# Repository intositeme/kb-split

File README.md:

# kb-split

Big thanks to guys on #QMK discord #hardward channel.

Very first PCB ever designed and produced. 6 cols x 4 rows + 2 extra switch & rotary Encoder
Split olkb keyboard runninf QMK Firmware

Initially designed to use Fischer EGG 0B(board side) with FGG 0B cables, though very expensive ( connectors alone are $40usd+). Added TRS footprint.

Board is reversible, though MCU sits only on 1 side.

- ATmega32u4-AU
- all leds Sk6812
- RGB Underglow & per key RGB
- 1x E11 rotary encoder

* Space bar fits up to 2u but no stabilizers

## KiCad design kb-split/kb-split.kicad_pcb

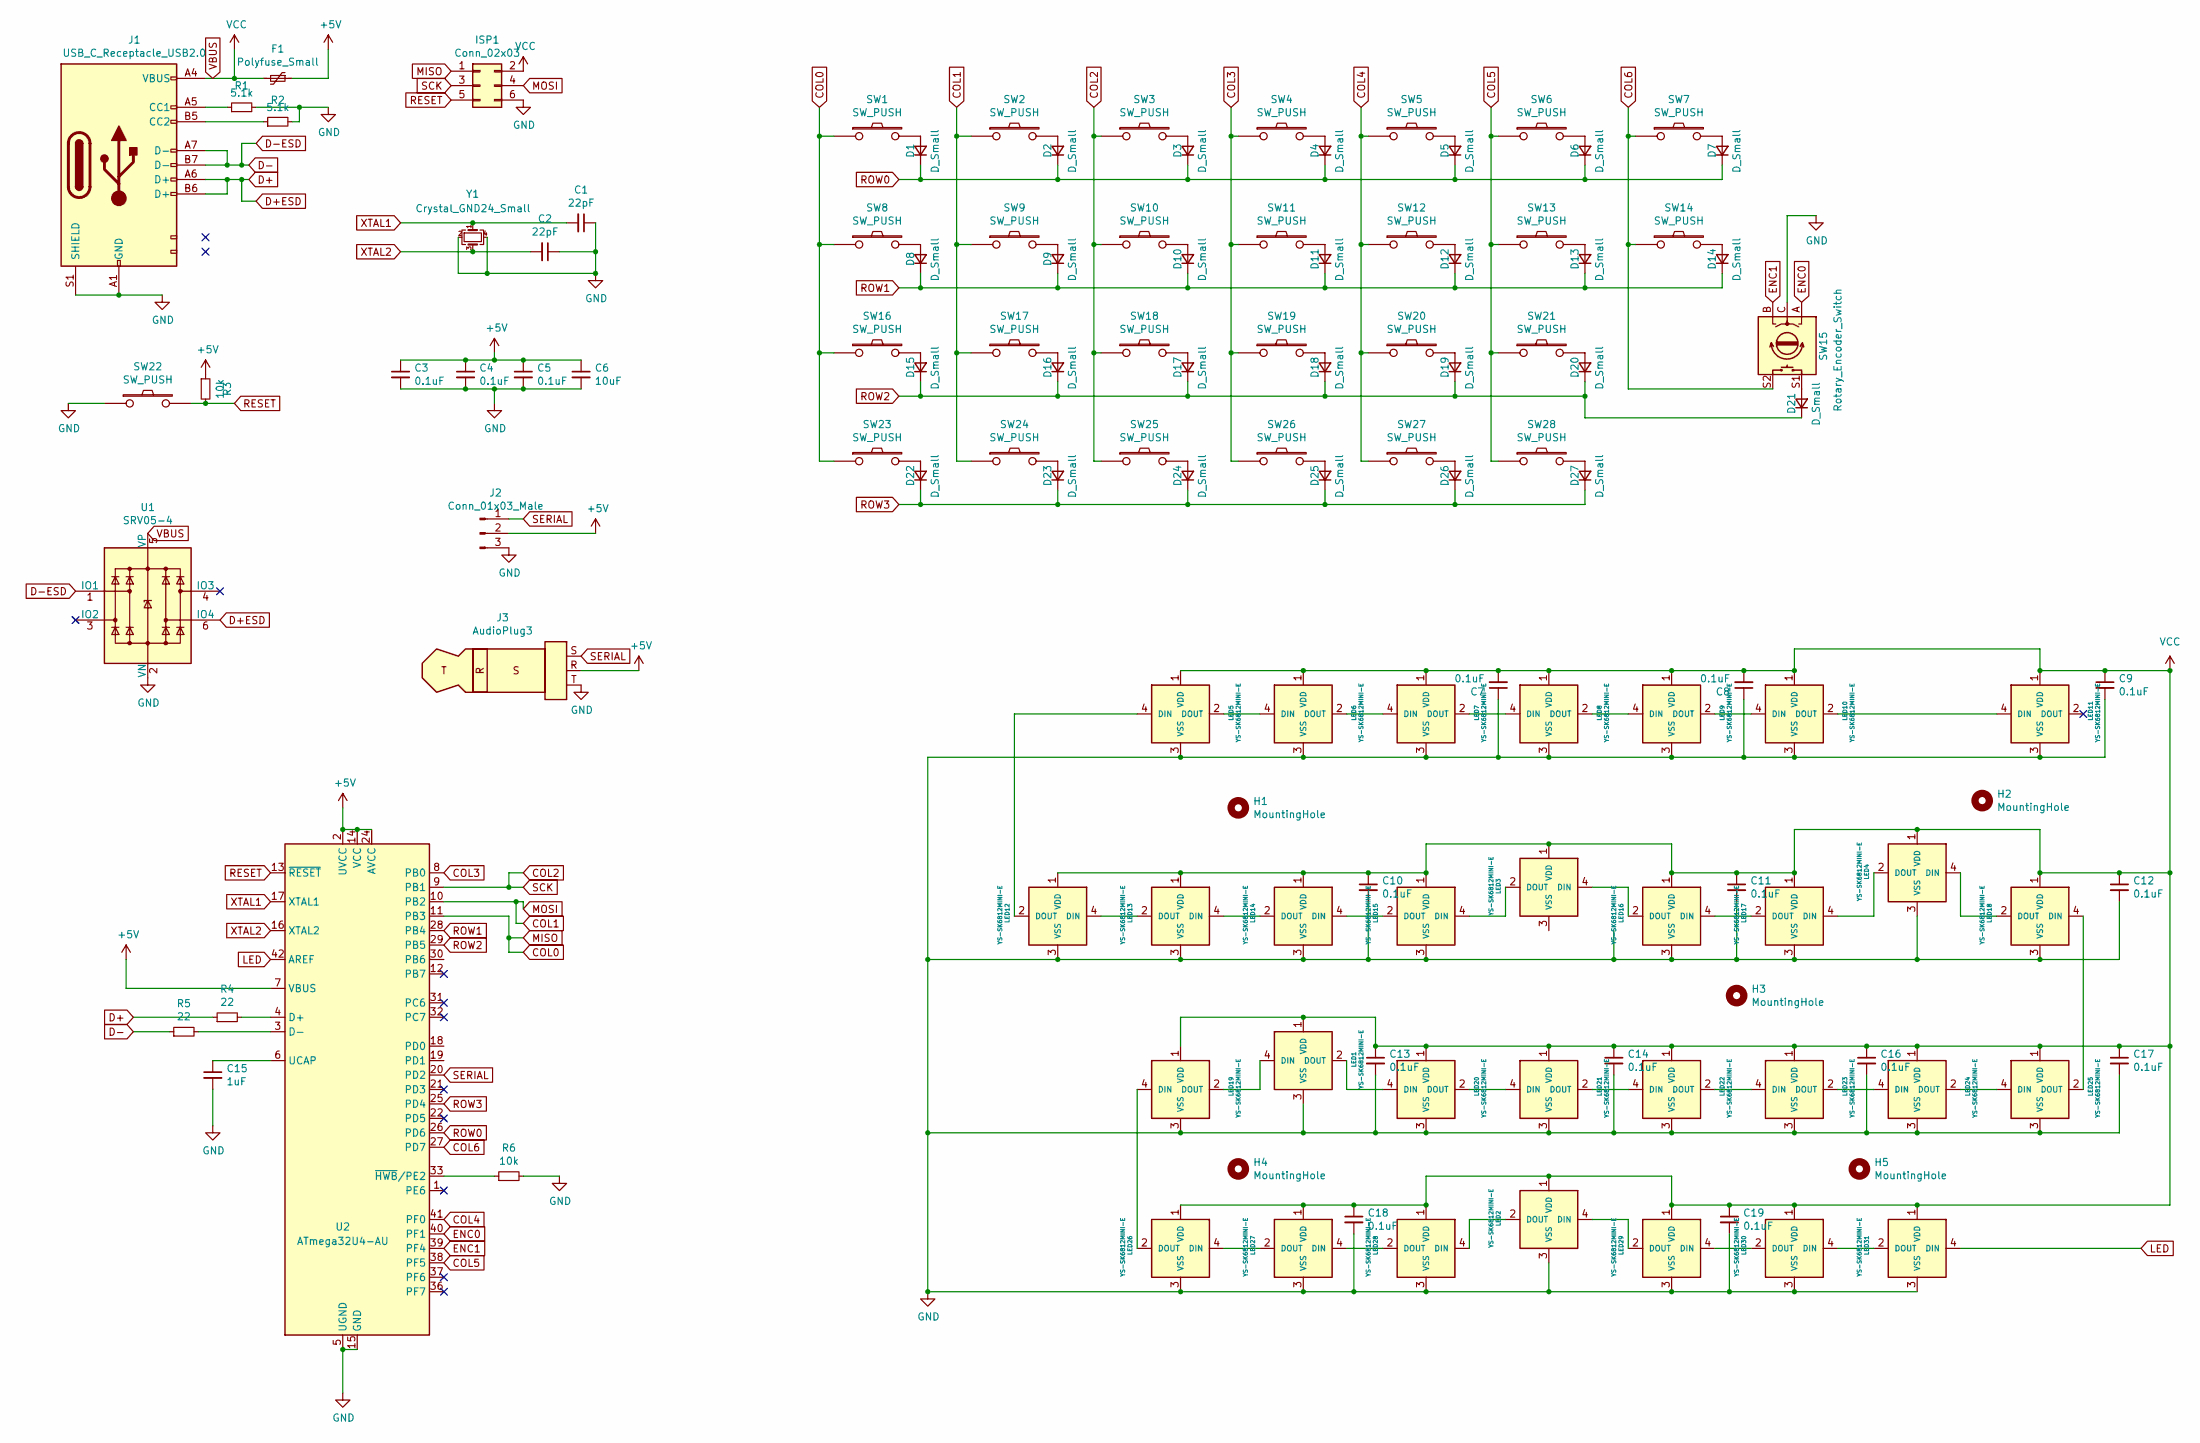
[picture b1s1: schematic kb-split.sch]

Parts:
C1, C2: 22pF; C-0805_2012Metric
C3, C4, C5, C7, C8, C9, C10, C11, C12, C13, C14, C16, C17, C18, C19: 0.1uF; C-0805_2012Metric
C6: 10uF; C-0805_2012Metric
C15: 1uF; C-0805_2012Metric
D1, D2, D3, D4, D5, D6, D7, D8, D9, D10, D11, D12, D13, D14, D15, D16, D17, D18, D19, D20, D21, D22, D23, D24, D25, D26, D27: D_Small; D_SOD-123
F1: Polyfuse_Small; Fuse_1206_3216Metric
H1, H2, H3, H4, H5: MountingHole; M2_HOLE_v3
ISP1: Conn_02x03; PinSocket_2x03_P2.54mm_Vertical
J1: USB_C_Receptacle_USB2.0; HRO-TYPE-C-31-M-12-HandSoldering-NoSBU
J2: Conn_01x03_Male; PinSocket_1x03_P2.54mm_Horizontal
J3: AudioPlug3; PJ-3136-B
LED1, LED2, LED3, LED4, LED25: YS-SK6812MINI-E; SK6812Mini-E
LED5, LED6, LED7, LED8, LED9, LED10, LED11, LED12, LED13, LED14, LED15, LED16, LED17, LED18, LED19, LED20, LED21, LED22, LED23, LED24, LED26, LED27, LED28, LED29, LED30, LED31: YS-SK6812MINI-E; MX-1U-SK6812Mini-E
R1, R2: 5.1k; R-0805_2012Metric
R3, R6: 10k; R-0805_2012Metric
R4, R5: 22; R-0805_2012Metric
SW1, SW2, SW3, SW4, SW5, SW6, SW7, SW8, SW9, SW10, SW11, SW12, SW13, SW14, SW16, SW17, SW18, SW19, SW20, SW21, SW23, SW24, SW25, SW26, SW27, SW28: SW_PUSH; MX-1U-Hotswap
SW15: Rotary_Encoder_Switch; MX-1U-EC11_Switch
SW22: SW_PUSH; SMD_Push
U1: SRV05-4; SOT-23-6
U2: ATmega32U4-AU; TQFP-44_10x10mm_P0.8mm
Y1: Crystal_GND24_Small; Reversible-Crystal_SMD_3225-4pin_3.2x2.5mm

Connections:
+5V: C3.1, C4.1, C5.1, C6.1, F1.1, J2.2, J3.R, R3.1, U2.2 (UVCC), U2.7 (VBUS), U2.14 (VCC), U2.24 (AVCC), U2.34 (VCC), U2.44 (AVCC)
COL0: ISP1.1, SW1.1, SW8.1, SW16.1, SW23.1, U2.11 (PB3)
COL1: ISP1.4, SW2.1, SW9.1, SW17.1, SW24.1, U2.10 (PB2)
COL2: ISP1.3, SW3.1, SW10.1, SW18.1, SW25.1, U2.9 (PB1)
COL3: SW4.1, SW11.1, SW19.1, SW26.1, U2.8 (PB0)
COL4: SW5.1, SW12.1, SW20.1, SW27.1, U2.41 (PF0)
COL5: SW6.1, SW13.1, SW21.1, SW28.1, U2.38 (PF5)
COL6: SW7.1, SW14.1, SW15.S2, U2.27 (PD7)
D+: J1.A6 (D+), J1.B6 (D+), R4.1, U1.6 (IO4)
D-: J1.A7 (D-), J1.B7 (D-), R5.1, U1.1 (IO1)
ENC0: SW15.A, U2.40 (PF1)
ENC1: SW15.B, U2.39 (PF4)
GND: C1.1, C2.1, C3.2, C4.2, C5.2, C6.2, C7.1, C8.1, C9.2, C10.2, C11.2, C12.2, C13.2, C14.2, C15.2, C16.2, C17.2, C18.2, C19.2, ISP1.6, J1.A1 (GND), J1.B1 (GND), J1.S1 (SHIELD), J2.3, J3.T, LED1.3 (VSS), LED2.3 (VSS), LED4.3 (VSS), LED5.3 (VSS), LED6.3 (VSS), LED7.3 (VSS), LED8.3 (VSS), LED9.3 (VSS), LED10.3 (VSS), LED11.3 (VSS), LED12.3 (VSS), LED13.3 (VSS), LED14.3 (VSS), LED15.3 (VSS), LED16.3 (VSS), LED17.3 (VSS), LED18.3 (VSS), LED19.3 (VSS), LED20.3 (VSS), LED21.3 (VSS), LED22.3 (VSS), LED23.3 (VSS), LED24.3 (VSS), LED25.3 (VSS), LED26.3 (VSS), LED27.3 (VSS), LED28.3 (VSS), LED29.3 (VSS), LED30.3 (VSS), LED31.3 (VSS), R1.2, R2.2, R6.2, SW15.C, SW22.1, U1.2 (VN), U2.5 (UGND), U2.15 (GND), U2.23 (GND), U2.35 (GND), U2.43 (GND), Y1.2, Y1.4
LED: LED31.4 (DIN), U2.42 (AREF)
unnamed: C15.1, U2.6 (UCAP)
unnamed: D1.2 (A), SW1.2
unnamed: D2.2 (A), SW2.2
unnamed: D3.2 (A), SW3.2
unnamed: D4.2 (A), SW4.2
unnamed: D5.2 (A), SW5.2
unnamed: D6.2 (A), SW6.2
unnamed: D7.2 (A), SW7.2
unnamed: D8.2 (A), SW8.2
unnamed: D9.2 (A), SW9.2
unnamed: D10.2 (A), SW10.2
unnamed: D11.2 (A), SW11.2
unnamed: D12.2 (A), SW12.2
unnamed: D13.2 (A), SW13.2
unnamed: D14.2 (A), SW14.2
unnamed: D15.2 (A), SW16.2
unnamed: D16.2 (A), SW17.2
unnamed: D17.2 (A), SW18.2
unnamed: D18.2 (A), SW19.2
unnamed: D19.2 (A), SW20.2
unnamed: D20.2 (A), SW21.2
unnamed: D21.2 (A), SW15.S1
unnamed: D22.2 (A), SW23.2
unnamed: D23.2 (A), SW24.2
unnamed: D24.2 (A), SW25.2
unnamed: D25.2 (A), SW26.2
unnamed: D26.2 (A), SW27.2
unnamed: D27.2 (A), SW28.2
unnamed: J1.A5 (CC1), R1.1
unnamed: J1.B5 (CC2), R2.1
unnamed: LED1.2 (DOUT), LED20.4 (DIN)
unnamed: LED1.4 (DIN), LED19.2 (DOUT)
unnamed: LED2.2 (DOUT), LED28.4 (DIN)
unnamed: LED2.4 (DIN), LED29.2 (DOUT)
unnamed: LED5.2 (DOUT), LED6.4 (DIN)
unnamed: LED6.2 (DOUT), LED7.4 (DIN)
unnamed: LED7.2 (DOUT), LED8.4 (DIN)
unnamed: LED8.2 (DOUT), LED9.4 (DIN)
unnamed: LED10.2 (DOUT), LED11.4 (DIN)
unnamed: LED9.2 (DOUT), LED10.4 (DIN)
unnamed: LED5.4 (DIN), LED12.2 (DOUT)
unnamed: LED12.4 (DIN), LED13.2 (DOUT)
unnamed: LED13.4 (DIN), LED14.2 (DOUT)
unnamed: LED14.4 (DIN), LED15.2 (DOUT)
unnamed: LED3.2 (DOUT), LED15.4 (DIN)
unnamed: LED3.4 (DIN), LED16.2 (DOUT)
unnamed: LED16.4 (DIN), LED17.2 (DOUT)
unnamed: LED4.2 (DOUT), LED17.4 (DIN)
unnamed: LED4.4 (DIN), LED18.2 (DOUT)
unnamed: LED18.4 (DIN), LED25.2 (DOUT)
unnamed: LED19.4 (DIN), LED26.2 (DOUT)
unnamed: LED20.2 (DOUT), LED21.4 (DIN)
unnamed: LED21.2 (DOUT), LED22.4 (DIN)
unnamed: LED22.2 (DOUT), LED23.4 (DIN)
unnamed: LED23.2 (DOUT), LED24.4 (DIN)
unnamed: LED24.2 (DOUT), LED25.4 (DIN)
unnamed: LED26.4 (DIN), LED27.2 (DOUT)
unnamed: LED27.4 (DIN), LED28.2 (DOUT)
unnamed: LED29.4 (DIN), LED30.2 (DOUT)
unnamed: LED30.4 (DIN), LED31.2 (DOUT)
unnamed: R4.2, U2.4 (D+)
unnamed: R5.2, U2.3 (D-)
unnamed: R6.1, U2.33 (~HWB~/PE2)
RESET: ISP1.5, R3.2, SW22.2, U2.13 (~RESET)
ROW0: D1.1 (K), D2.1 (K), D3.1 (K), D4.1 (K), D5.1 (K), D6.1 (K), D7.1 (K), U2.26 (PD6)
ROW1: D8.1 (K), D9.1 (K), D10.1 (K), D11.1 (K), D12.1 (K), D13.1 (K), D14.1 (K), U2.28 (PB4)
ROW2: D15.1 (K), D16.1 (K), D17.1 (K), D18.1 (K), D19.1 (K), D20.1 (K), D21.1 (K), U2.29 (PB5)
ROW3: D22.1 (K), D23.1 (K), D24.1 (K), D25.1 (K), D26.1 (K), D27.1 (K), U2.25 (PD4)
SERIAL: J2.1, J3.S, U2.20 (PD2)
VBUS: C7.2, C8.2, C9.1, C10.1, C11.1, C12.1, C13.1, C14.1, C16.1, C17.1, C18.1, C19.1, F1.2, ISP1.2, J1.A4 (VBUS), J1.B4 (VBUS), LED1.1 (VDD), LED2.1 (VDD), LED3.1 (VDD), LED4.1 (VDD), LED5.1 (VDD), LED6.1 (VDD), LED7.1 (VDD), LED8.1 (VDD), LED9.1 (VDD), LED10.1 (VDD), LED11.1 (VDD), LED12.1 (VDD), LED13.1 (VDD), LED14.1 (VDD), LED15.1 (VDD), LED16.1 (VDD), LED17.1 (VDD), LED18.1 (VDD), LED19.1 (VDD), LED20.1 (VDD), LED21.1 (VDD), LED22.1 (VDD), LED23.1 (VDD), LED24.1 (VDD), LED25.1 (VDD), LED26.1 (VDD), LED27.1 (VDD), LED28.1 (VDD), LED29.1 (VDD), LED30.1 (VDD), LED31.1 (VDD), U1.5 (VP)
XTAL1: C1.2, U2.17 (XTAL1), Y1.1
XTAL2: C2.2, U2.16 (XTAL2), Y1.3

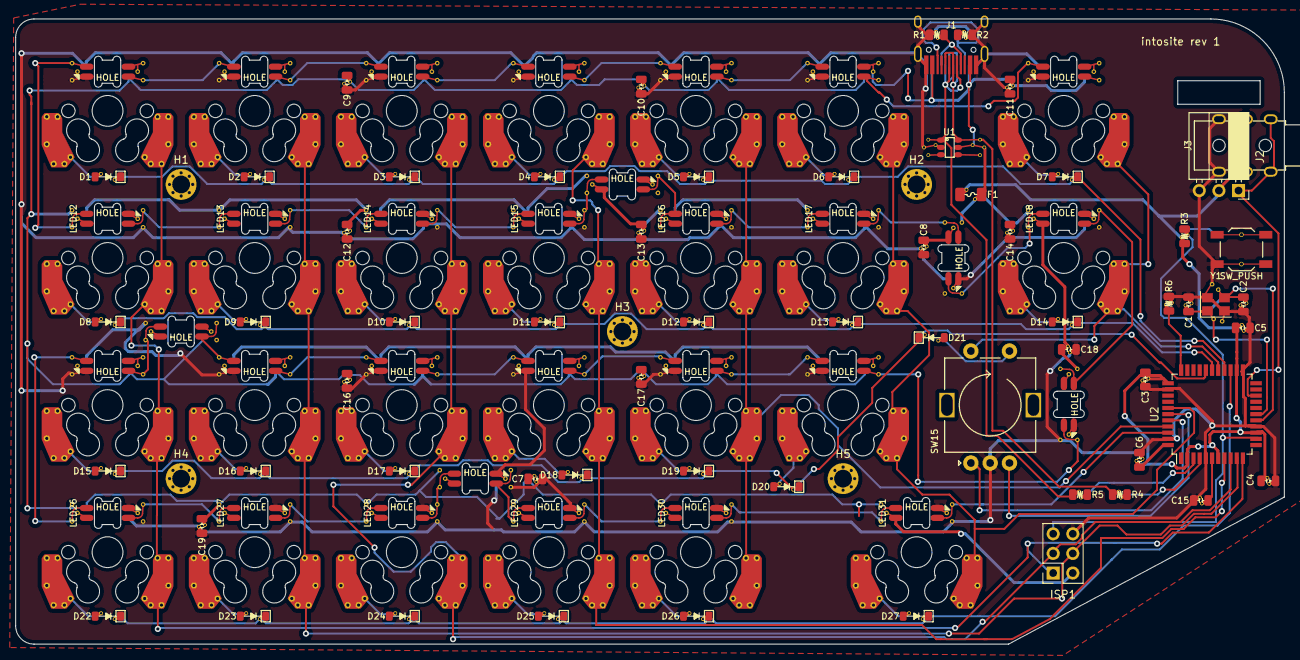
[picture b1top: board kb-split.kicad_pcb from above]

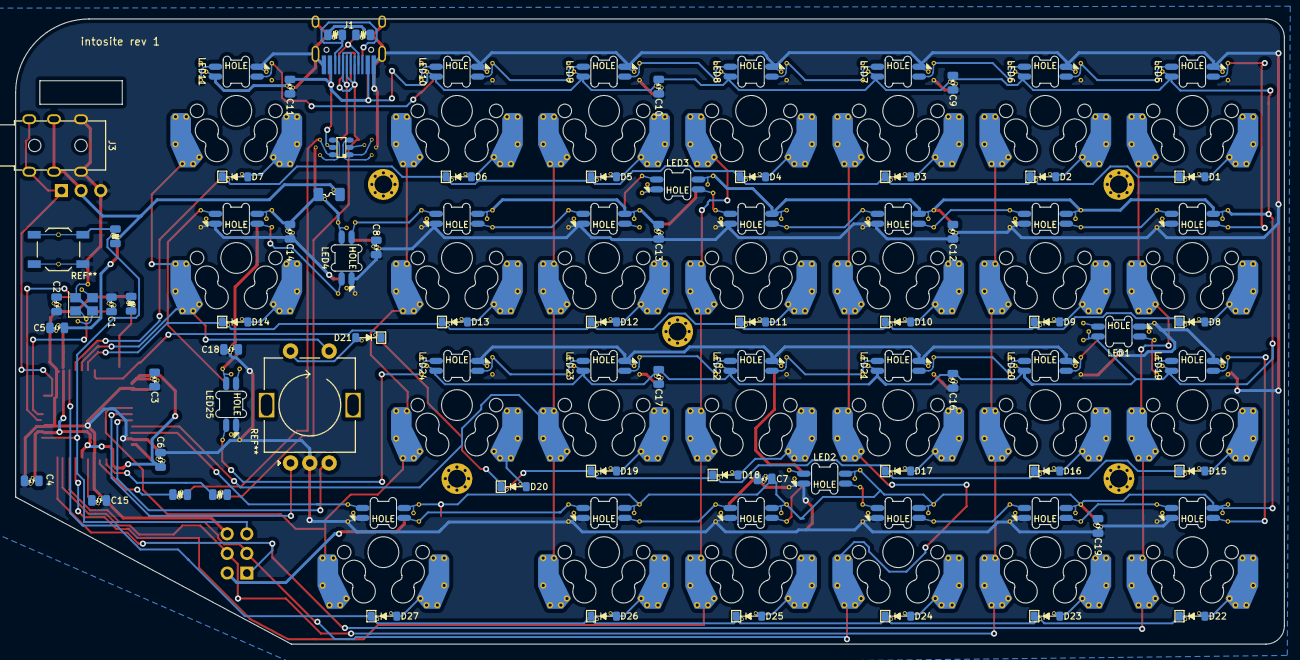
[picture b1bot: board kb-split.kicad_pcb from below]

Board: 2 copper layers, 164.3 x 80.9 mm, 124 parts (13 on the bottom side), 86 nets.

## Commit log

2021-01-17 Schematic updates
2021-01-17 Added Layout Template
2021-01-17 Added USB C schematic
2021-01-18 redo schematic to remove eliteC and use atmega32u4 directly
2021-01-18 update pdf
2021-01-19 Create reversible Cystal footprint
2021-01-19 Layout components
2021-01-19 Adding trace
2021-01-20 Done routing.
2021-01-20 Rev 1. Sent to manufacture. Added ground fills
2021-01-20 Created BOM
2021-01-21 Added trs and fix gerbers export
2021-01-21 save
2021-01-21 Update gerber export. Passed JLC verification
2021-01-24 Added render case
